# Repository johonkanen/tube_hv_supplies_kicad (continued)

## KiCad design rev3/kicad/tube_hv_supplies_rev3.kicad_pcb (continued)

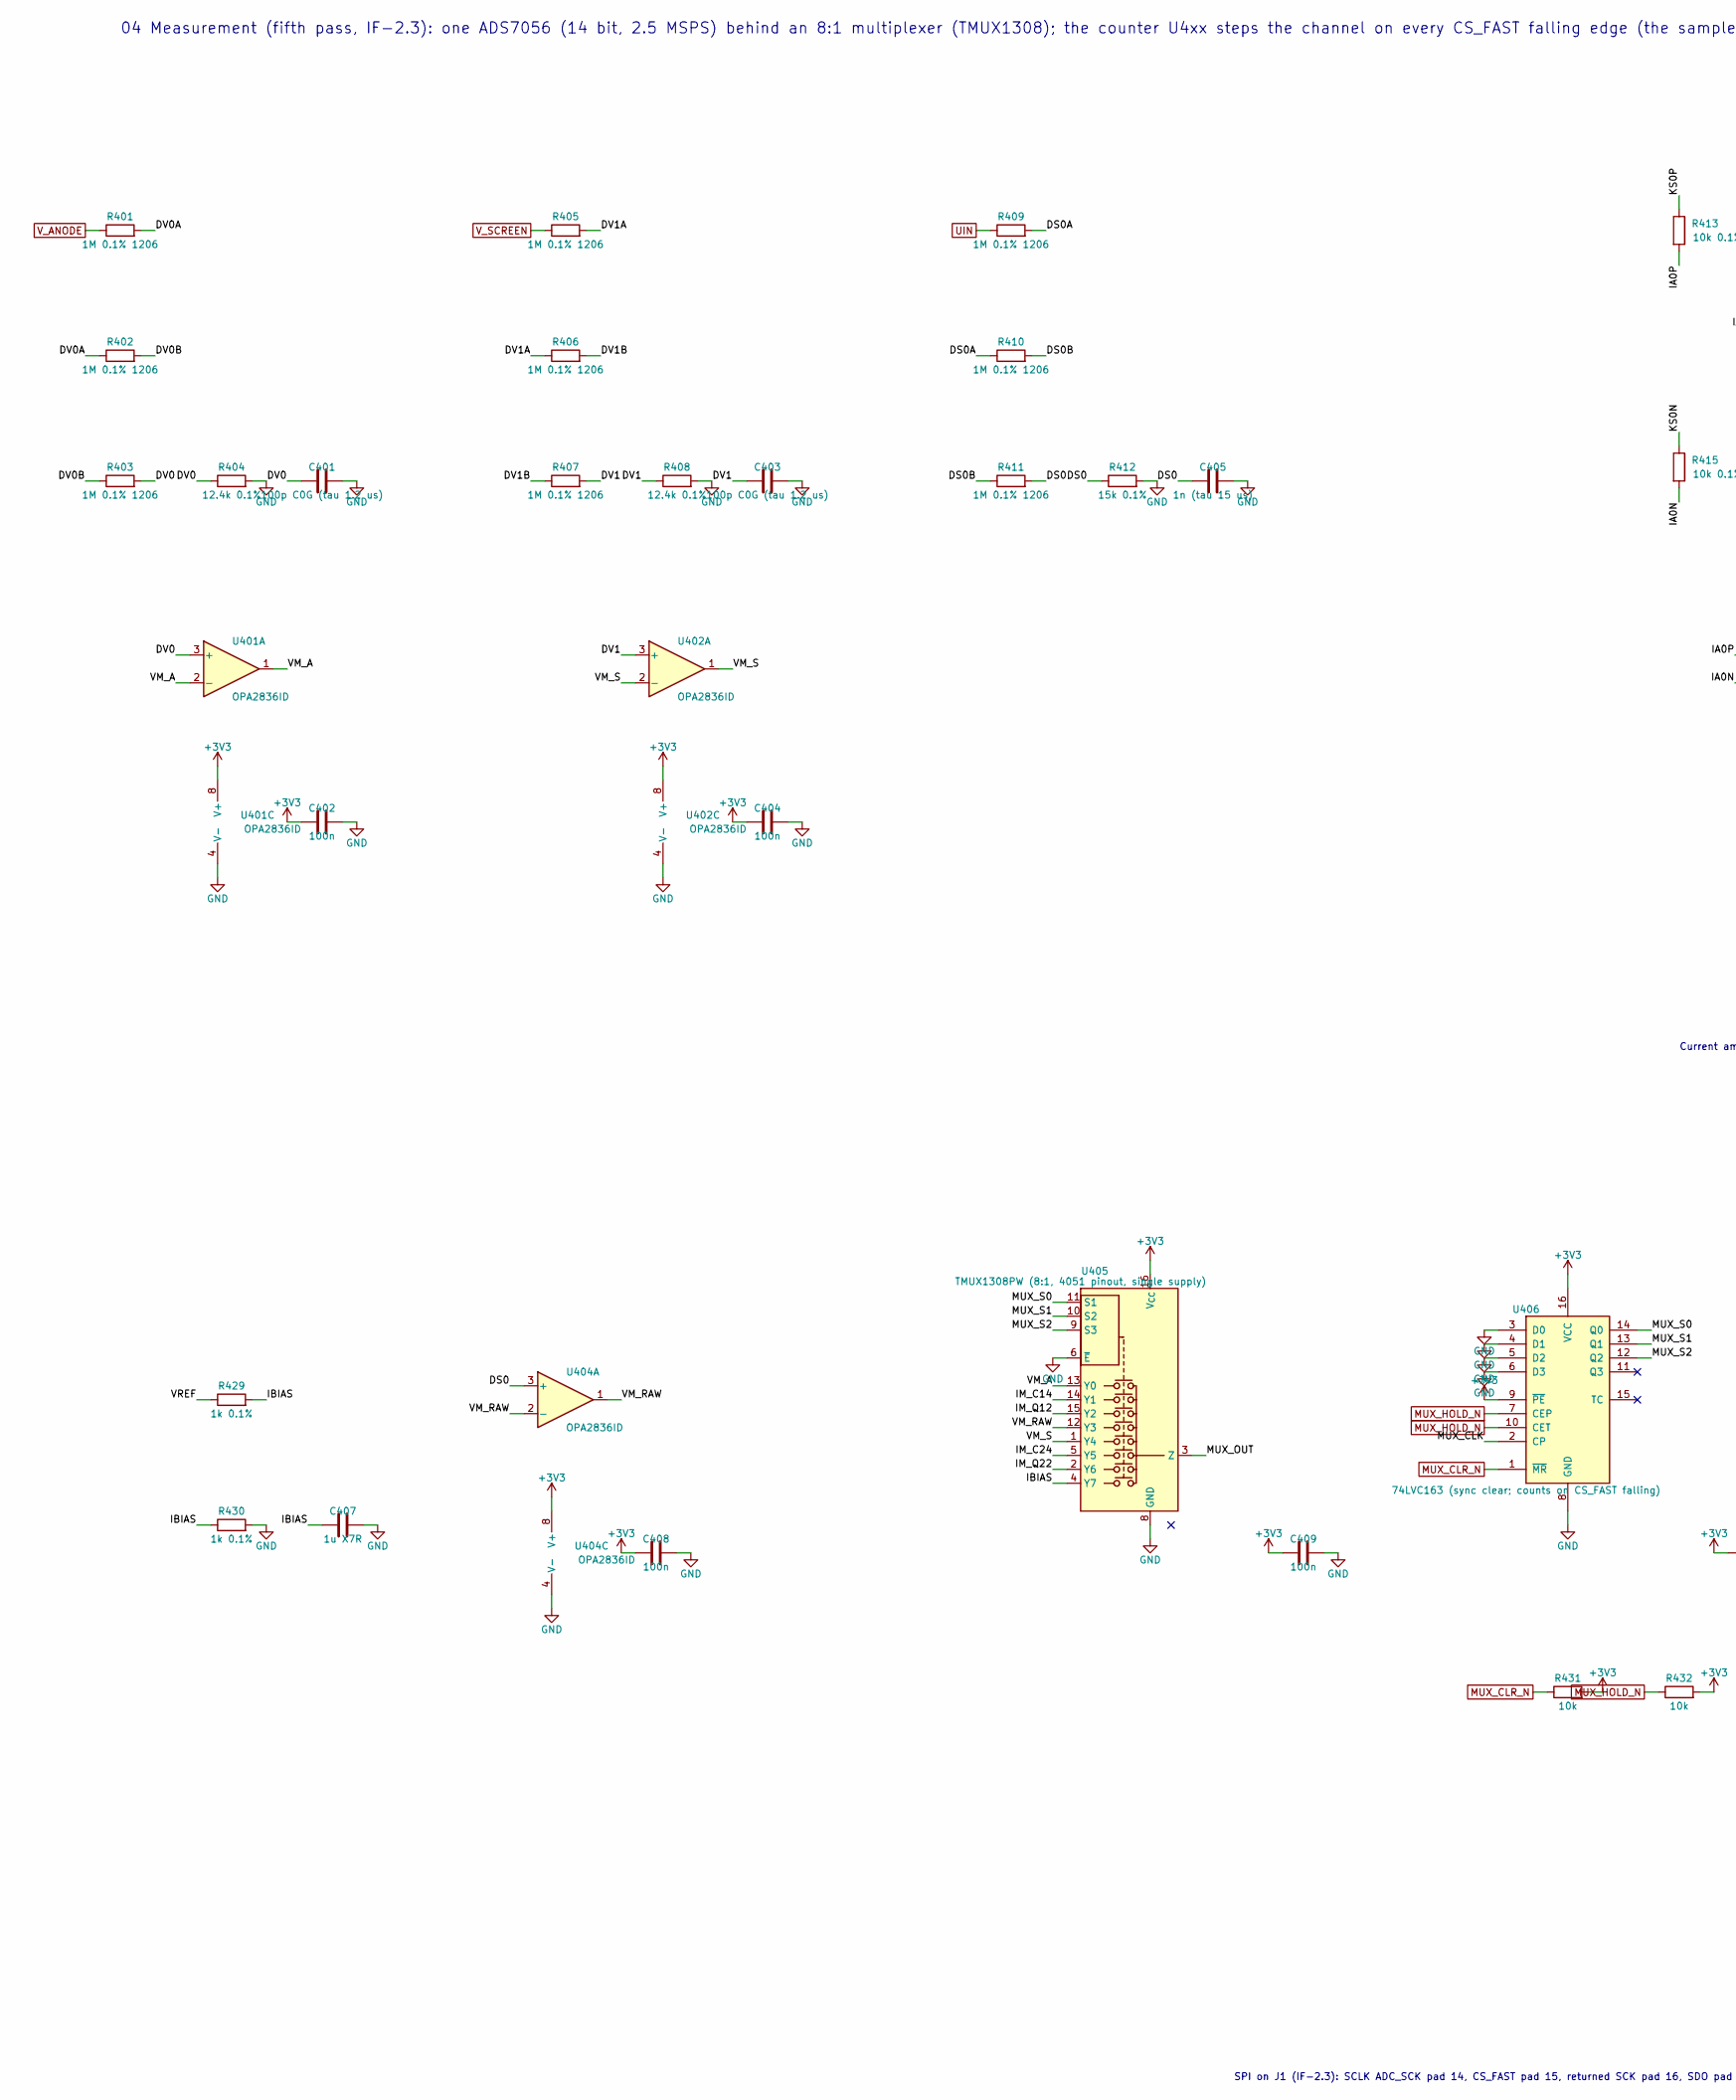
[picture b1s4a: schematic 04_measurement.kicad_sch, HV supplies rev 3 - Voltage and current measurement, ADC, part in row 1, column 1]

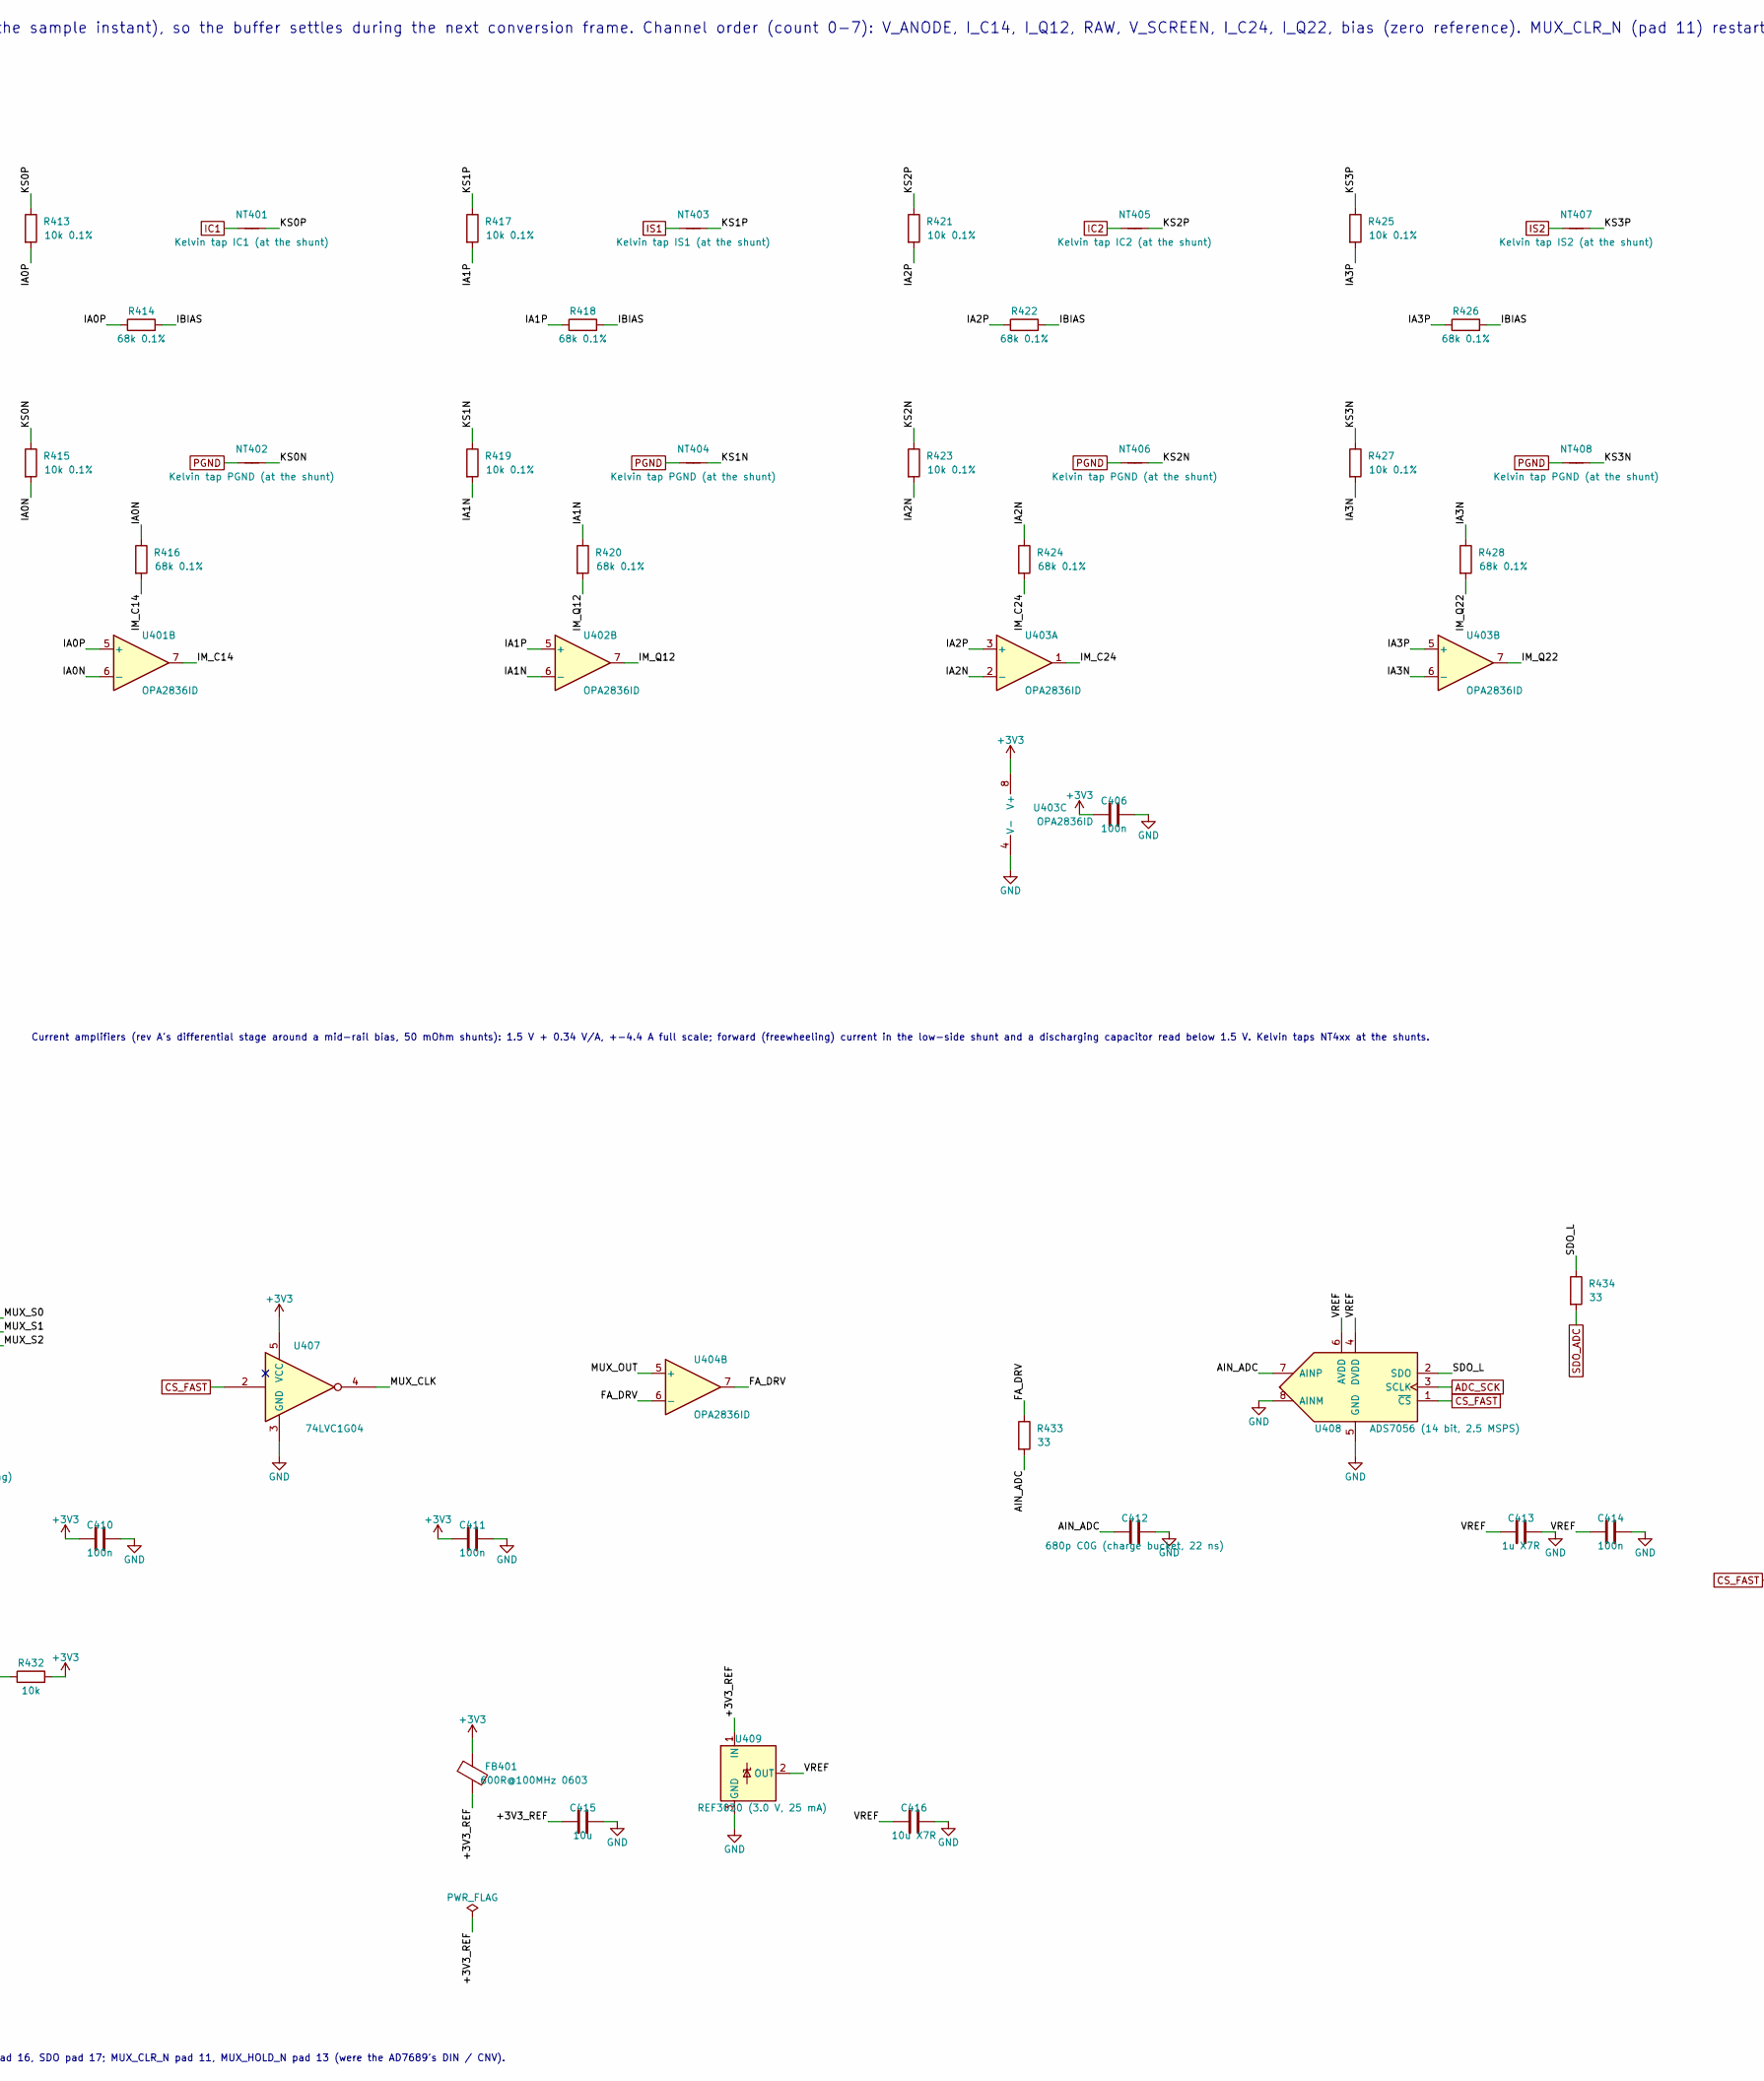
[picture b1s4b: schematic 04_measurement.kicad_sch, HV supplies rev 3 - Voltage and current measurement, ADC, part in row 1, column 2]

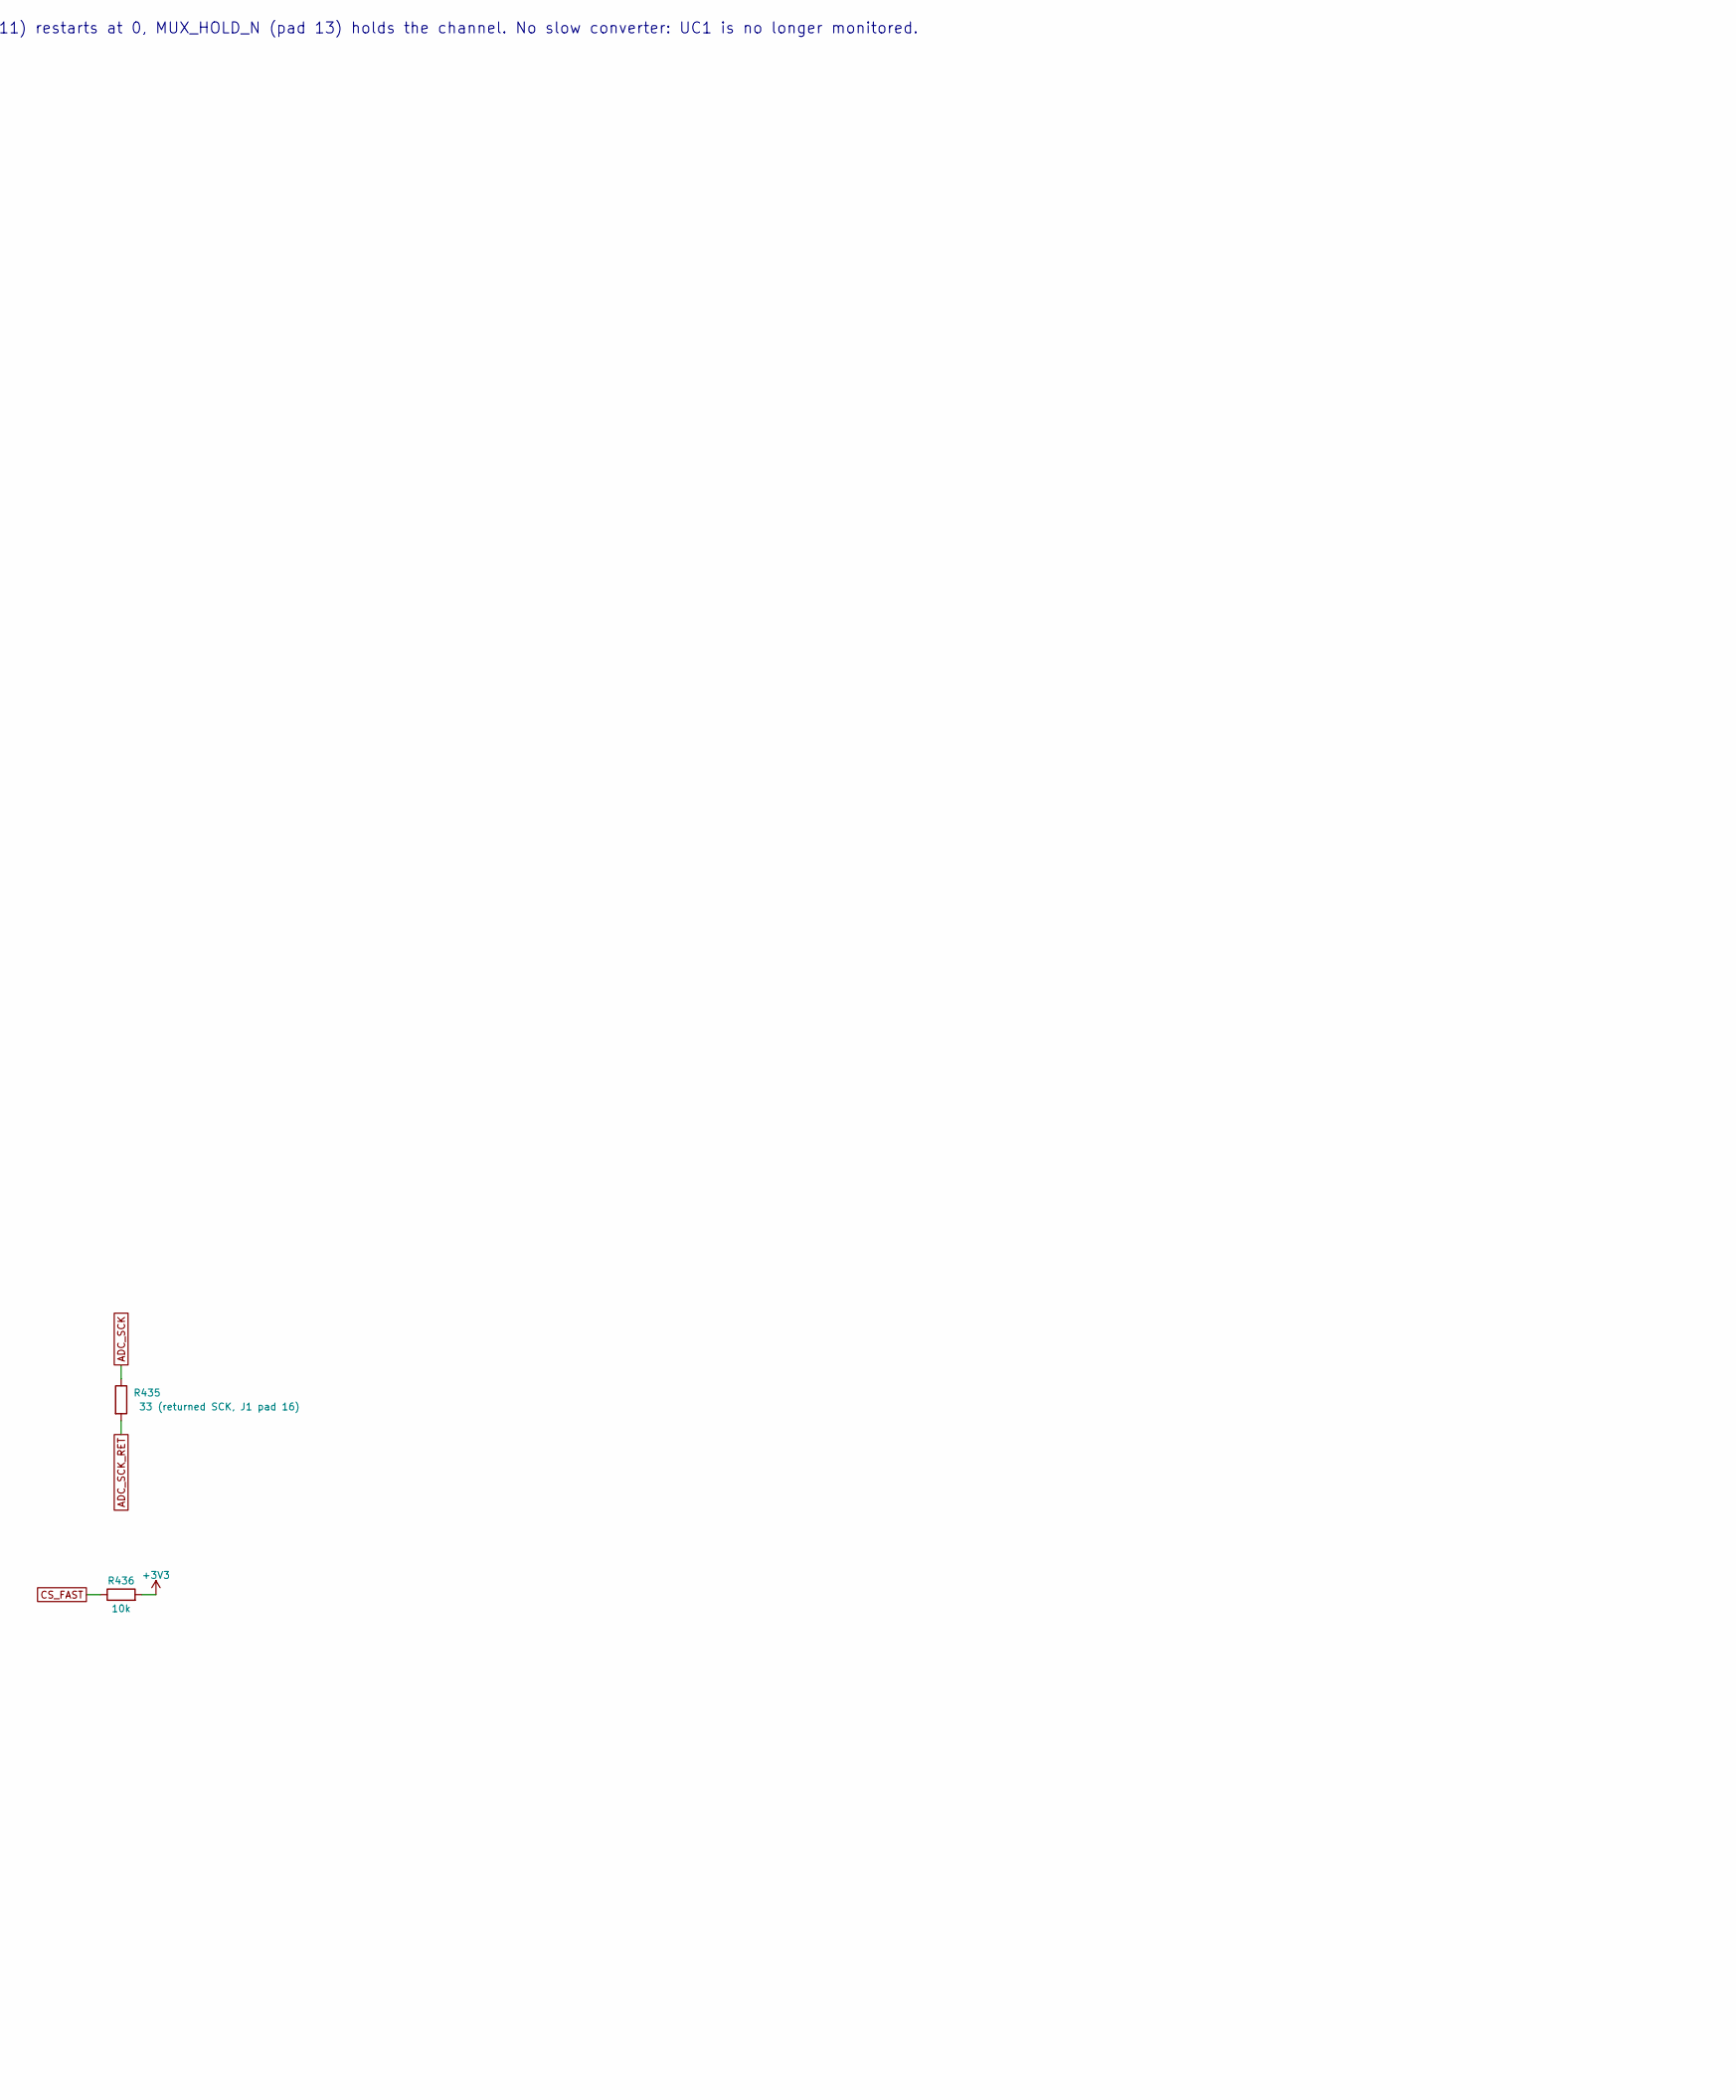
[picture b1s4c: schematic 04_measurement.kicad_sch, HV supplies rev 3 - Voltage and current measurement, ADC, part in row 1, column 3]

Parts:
C401, C403: 100p C0G (tau 1.2 us); C_0603_1608Metric
C402, C404, C406, C408, C409, C410, C411, C414: 100n; C_0603_1608Metric
C405: 1n (tau 15 us); C_0603_1608Metric
C407, C413: 1u X7R; C_0603_1608Metric
C412: 680p C0G (charge bucket, 22 ns); C_0603_1608Metric
C415: 10u; C_0805_2012Metric
C416: 10u X7R; C_0805_2012Metric
FB401: 600R@100MHz 0603; L_0603_1608Metric
NT401: Kelvin tap IC1 (at the shunt); NetTie-2_SMD_Pad0.5mm
NT402, NT404, NT406, NT408: Kelvin tap PGND (at the shunt); NetTie-2_SMD_Pad0.5mm
NT403: Kelvin tap IS1 (at the shunt); NetTie-2_SMD_Pad0.5mm
NT405: Kelvin tap IC2 (at the shunt); NetTie-2_SMD_Pad0.5mm
NT407: Kelvin tap IS2 (at the shunt); NetTie-2_SMD_Pad0.5mm
R401, R402, R403, R405, R406, R407, R409, R410, R411: 1M 0.1% 1206; R_1206_3216Metric
R404, R408: 12.4k 0.1%; R_0603_1608Metric
R412: 15k 0.1%; R_0603_1608Metric
R413, R415, R417, R419, R421, R423, R425, R427: 10k 0.1%; R_0603_1608Metric
R414, R416, R418, R420, R422, R424, R426, R428: 68k 0.1%; R_0603_1608Metric
R429, R430: 1k 0.1%; R_0603_1608Metric
R431, R432, R436: 10k; R_0603_1608Metric
R433, R434: 33; R_0603_1608Metric
R435: 33 (returned SCK, J1 pad 16); R_0603_1608Metric
U401, U402, U403, U404: OPA2836ID; SOIC-8_3.9x4.9mm_P1.27mm; MPN OPA2836IDR
U405: TMUX1308PW (8:1, 4051 pinout, single supply); TSSOP-16_4.4x5mm_P0.65mm; MPN TMUX1308PWR
U406: 74LVC163 (sync clear; counts on CS_FAST falling); TSSOP-16_4.4x5mm_P0.65mm; MPN SN74LVC163APWR
U407: 74LVC1G04; SOT-23-5; MPN SN74LVC1G04DBVR
U408: ADS7056 (14 bit, 2.5 MSPS); Texas_UQFN-8_1.5x1.5mm_P0.5mm; MPN ADS7056IRUGR
U409: REF3030 (3.0 V, 25 mA); SOT-23; MPN REF3030AIDBZR

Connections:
+3V3: C402.1, C404.1, C406.1, C408.1, C409.1, C410.1, C411.1, FB401.1, R431.2, R432.2, R436.2, U401.8 (V+), U402.8 (V+), U403.8 (V+), U404.8 (V+), U405.16 (V_{CC}), U406.9 (~PE), U406.16 (VCC), U407.5 (VCC); also elsewhere on the board
/04 Voltage and current measurement, ADC/+3V3_REF: C415.1, FB401.2, U409.1 (IN)
/04 Voltage and current measurement, ADC/AIN_ADC: C412.1, R433.2, U408.7 (AINP)
/04 Voltage and current measurement, ADC/DS0: C405.1, R411.2, R412.1, U404.3 (+)
/04 Voltage and current measurement, ADC/DS0A: R409.2, R410.1
/04 Voltage and current measurement, ADC/DS0B: R410.2, R411.1
/04 Voltage and current measurement, ADC/DV0: C401.1, R403.2, R404.1, U401.3 (+)
/04 Voltage and current measurement, ADC/DV0A: R401.2, R402.1
/04 Voltage and current measurement, ADC/DV0B: R402.2, R403.1
/04 Voltage and current measurement, ADC/DV1: C403.1, R407.2, R408.1, U402.3 (+)
/04 Voltage and current measurement, ADC/DV1A: R405.2, R406.1
/04 Voltage and current measurement, ADC/DV1B: R406.2, R407.1
/04 Voltage and current measurement, ADC/FA_DRV: R433.1, U404.6 (-), U404.7
/04 Voltage and current measurement, ADC/IA0N: R415.2, R416.1, U401.6 (-)
/04 Voltage and current measurement, ADC/IA0P: R413.2, R414.1, U401.5 (+)
/04 Voltage and current measurement, ADC/IA1N: R419.2, R420.1, U402.6 (-)
/04 Voltage and current measurement, ADC/IA1P: R417.2, R418.1, U402.5 (+)
/04 Voltage and current measurement, ADC/IA2N: R423.2, R424.1, U403.2 (-)
/04 Voltage and current measurement, ADC/IA2P: R421.2, R422.1, U403.3 (+)
/04 Voltage and current measurement, ADC/IA3N: R427.2, R428.1, U403.6 (-)
/04 Voltage and current measurement, ADC/IA3P: R425.2, R426.1, U403.5 (+)
/04 Voltage and current measurement, ADC/IBIAS: C407.1, R414.2, R418.2, R422.2, R426.2, R429.2, R430.1, U405.4 (Y7)
/04 Voltage and current measurement, ADC/IM_C14: R416.2, U401.7, U405.14 (Y1)
/04 Voltage and current measurement, ADC/IM_C24: R424.2, U403.1, U405.5 (Y5)
/04 Voltage and current measurement, ADC/IM_Q12: R420.2, U402.7, U405.15 (Y2)
/04 Voltage and current measurement, ADC/IM_Q22: R428.2, U403.7, U405.2 (Y6)
/04 Voltage and current measurement, ADC/KS0N: NT402.2, R415.1
/04 Voltage and current measurement, ADC/KS0P: NT401.2, R413.1
/04 Voltage and current measurement, ADC/KS1N: NT404.2, R419.1
/04 Voltage and current measurement, ADC/KS1P: NT403.2, R417.1
/04 Voltage and current measurement, ADC/KS2N: NT406.2, R423.1
/04 Voltage and current measurement, ADC/KS2P: NT405.2, R421.1
/04 Voltage and current measurement, ADC/KS3N: NT408.2, R427.1
/04 Voltage and current measurement, ADC/KS3P: NT407.2, R425.1
/04 Voltage and current measurement, ADC/MUX_CLK: U406.2 (CP), U407.4
/04 Voltage and current measurement, ADC/MUX_OUT: U404.5 (+), U405.3 (Z)
/04 Voltage and current measurement, ADC/MUX_S0: U405.11 (S1), U406.14 (Q0)
/04 Voltage and current measurement, ADC/MUX_S1: U405.10 (S2), U406.13 (Q1)
/04 Voltage and current measurement, ADC/MUX_S2: U405.9 (S3), U406.12 (Q2)
/04 Voltage and current measurement, ADC/SDO_L: R434.1, U408.2 (SDO)
/04 Voltage and current measurement, ADC/VM_A: U401.1, U401.2 (-), U405.13 (Y0)
/04 Voltage and current measurement, ADC/VM_RAW: U404.1, U404.2 (-), U405.12 (Y3)
/04 Voltage and current measurement, ADC/VM_S: U402.1, U402.2 (-), U405.1 (Y4)
/04 Voltage and current measurement, ADC/VREF: C413.1, C414.1, C416.1, R429.1, U408.4 (DVDD), U408.6 (AVDD), U409.2 (OUT)
ADC_SCK: R435.1, U408.3 (SCLK); also elsewhere on the board
ADC_SCK_RET: R435.2; also elsewhere on the board
CS_FAST: R436.1, U407.2, U408.1 (~CS); also elsewhere on the board
GND: C401.2, C402.2, C403.2, C404.2, C405.2, C406.2, C407.2, C408.2, C409.2, C410.2, C411.2, C412.2, C413.2, C414.2, C415.2, C416.2, R404.2, R408.2, R412.2, R430.2, U401.4 (V-), U402.4 (V-), U403.4 (V-), U404.4 (V-), U405.6 (~E), U405.8 (GND), U406.3 (D0), U406.4 (D1), U406.5 (D2), U406.6 (D3), U406.8 (GND), U407.3 (GND), U408.5 (GND), U408.8 (AINM), U409.3 (GND); also elsewhere on the board
IC1: NT401.1; also elsewhere on the board
IC2: NT405.1; also elsewhere on the board
IS1: NT403.1; also elsewhere on the board
IS2: NT407.1; also elsewhere on the board
MUX_CLR_N: R431.1, U406.1 (~MR); also elsewhere on the board
MUX_HOLD_N: R432.1, U406.7 (CEP), U406.10 (CET); also elsewhere on the board
PGND: NT402.1, NT404.1, NT406.1, NT408.1; also elsewhere on the board
SDO_ADC: R434.2; also elsewhere on the board
UIN: R409.1; also elsewhere on the board
V_ANODE: R401.1; also elsewhere on the board
V_SCREEN: R405.1; also elsewhere on the board

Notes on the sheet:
04 Measurement (fifth pass, IF-2.3): one ADS7056 (14 bit, 2.5 MSPS) behind an 8:1 multiplexer (TMUX1308); the counter U4xx steps the channel on every CS_FAST falling edge (the sample instant), so the buffer settles during the next conversion frame. Channel order (count 0-7): V_ANODE, I_C14, I_Q12, 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
Current amplifiers (rev A's differential stage around a mid-rail bias, 50 mOhm shunts): 1.5 V + 0.34 V/A, +-4.4 A full scale; forward (freewheeling) current in the low-side shunt and a discharging capacitor read below 1.5 V. Kelvin taps NT4xx at the shunts.
SPI on J1 (IF-2.3): SCLK ADC_SCK pad 14, CS_FAST pad 15, returned SCK pad 16, SDO pad 17; MUX_CLR_N pad 11, MUX_HOLD_N pad 13 (were the AD7689's DIN / CNV).

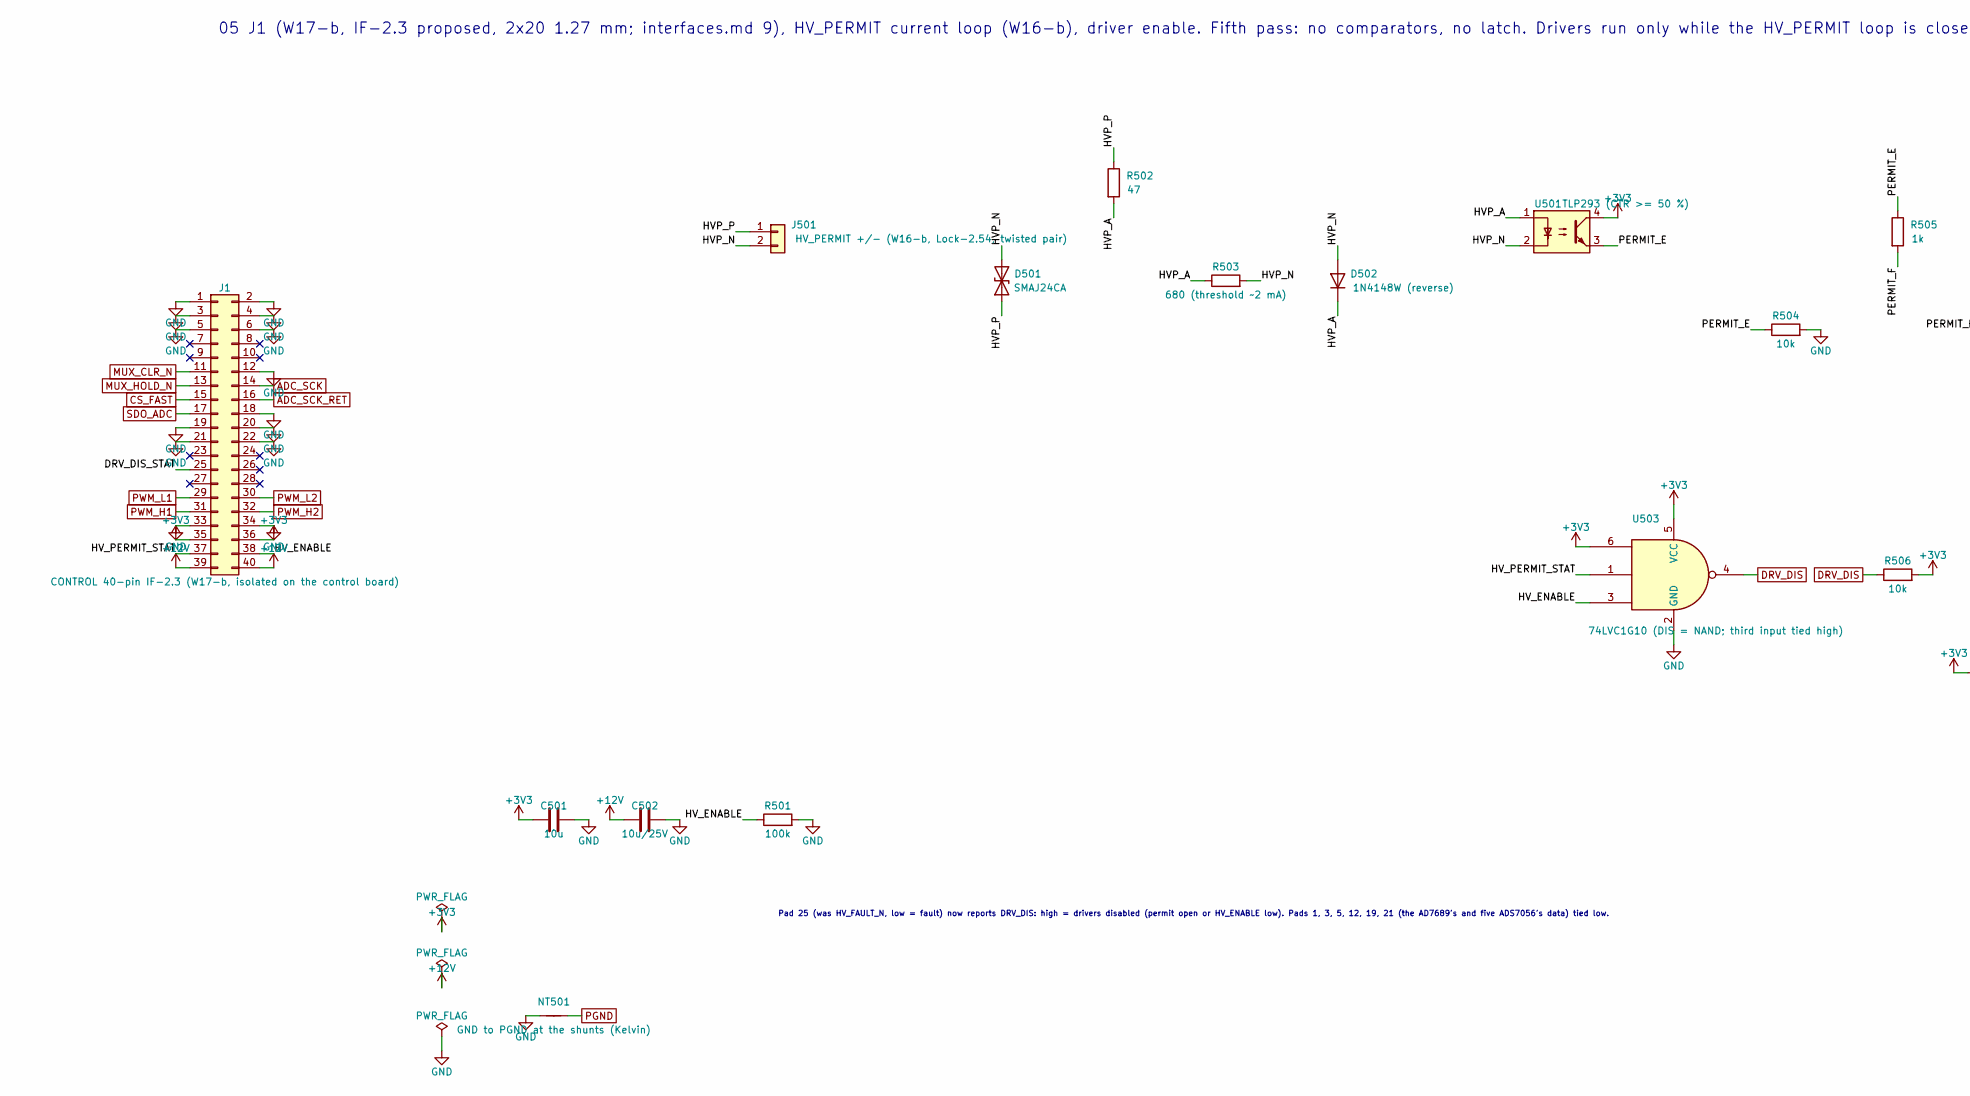
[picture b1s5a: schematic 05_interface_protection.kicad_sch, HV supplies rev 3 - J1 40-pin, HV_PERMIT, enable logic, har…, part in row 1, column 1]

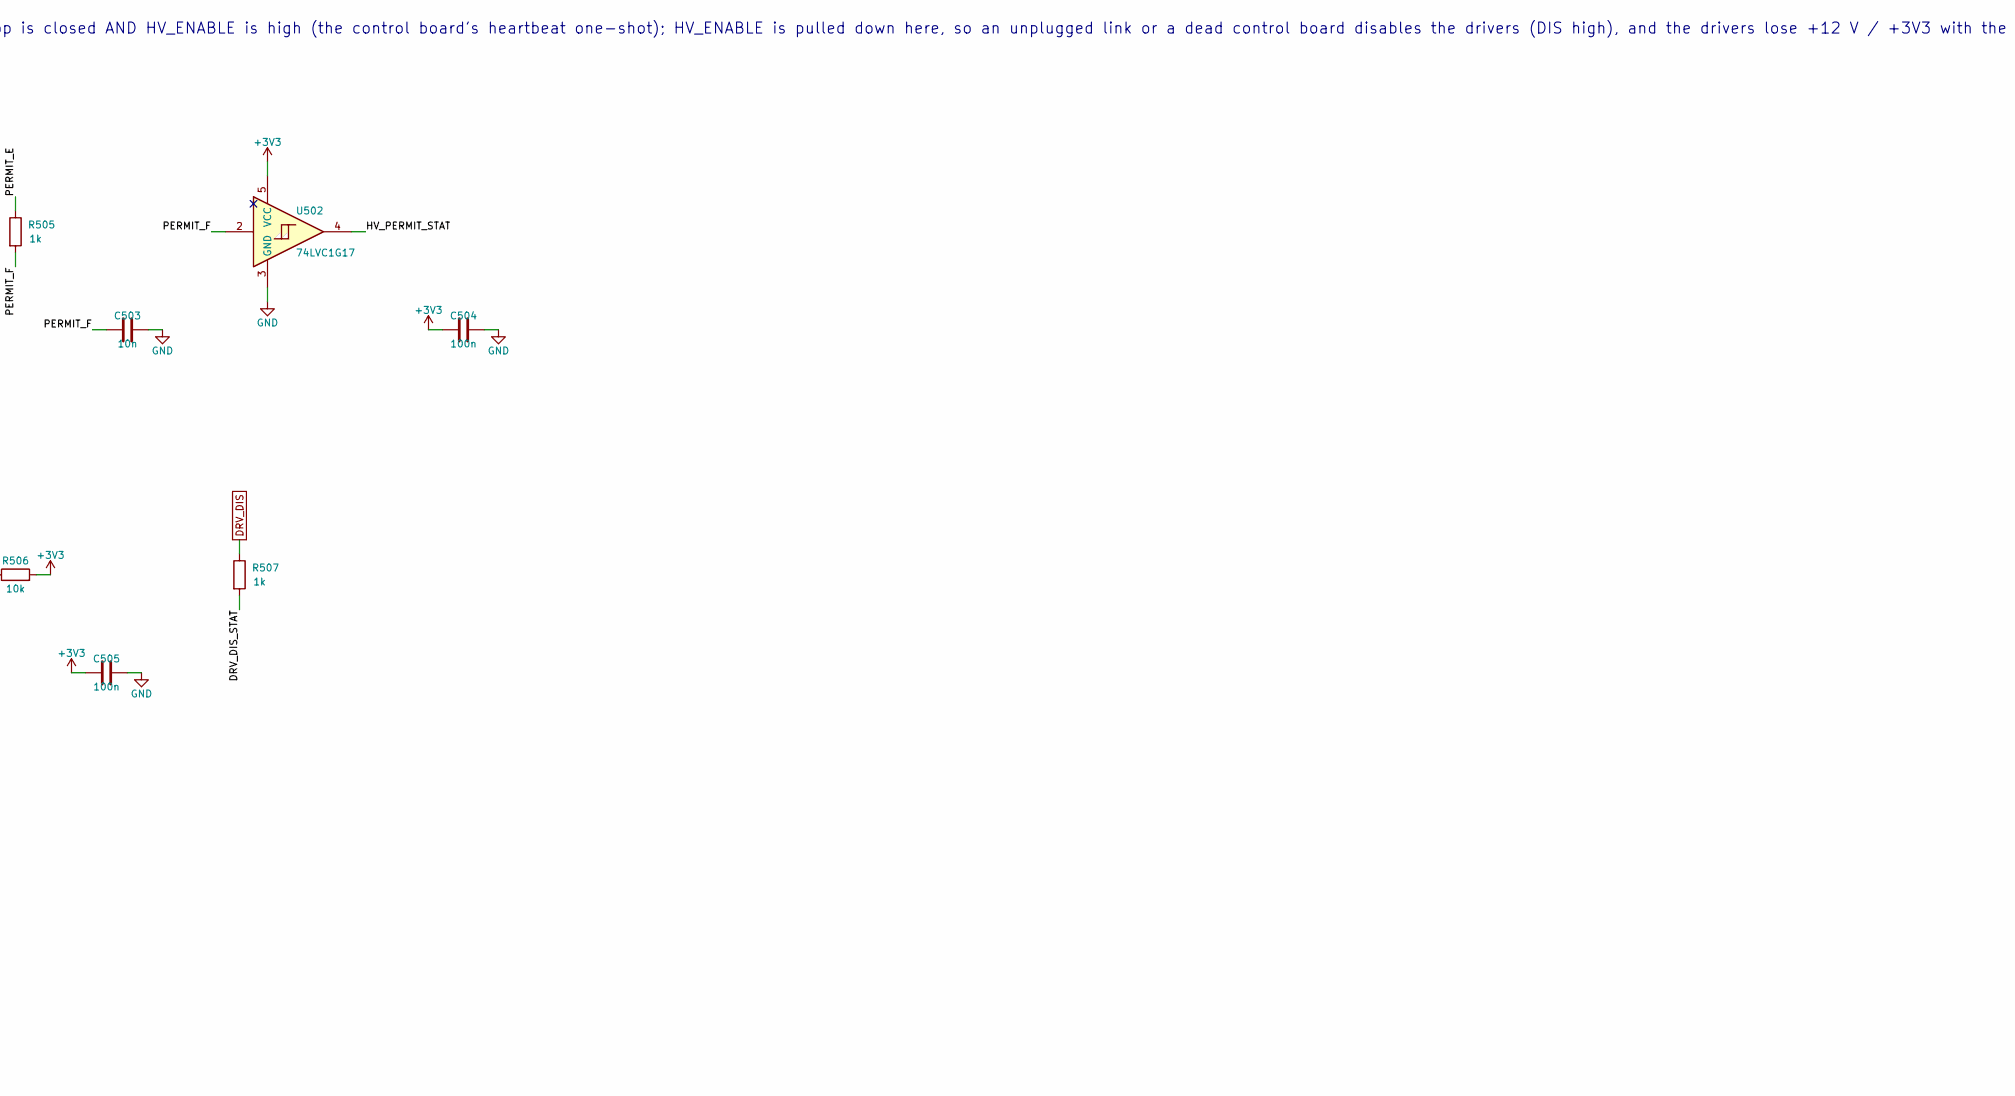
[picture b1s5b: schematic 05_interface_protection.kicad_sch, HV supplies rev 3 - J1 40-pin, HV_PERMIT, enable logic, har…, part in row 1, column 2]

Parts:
C501: 10u; C_0805_2012Metric
C502: 10u/25V; C_1206_3216Metric
C503: 10n; C_0603_1608Metric
C504, C505: 100n; C_0603_1608Metric
D501: SMAJ24CA; D_SMA; MPN SMAJ24CA
D502: 1N4148W (reverse); D_SOD-123; MPN 1N4148W
J1: CONTROL 40-pin IF-2.3 (W17-b, isolated on the con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; PinHeader_2x20_P1.27mm_Vertical; MPN Samtec SHF-120-01-L-D-TH
J501: HV_PERMIT +/- (W16-b, Lock-2.54, twisted pair); Molex_KK-254_AE-6410-02A_1x02_P2.54mm_Vertical; MPN Molex 22-27-2021
NT501: GND to PGND at the shunts (Kelvin); NetTie-2_SMD_Pad0.5mm
R501: 100k; R_0603_1608Metric
R502: 47; R_0603_1608Metric
R503: 680 (threshold ~2 mA); R_0603_1608Metric
R504, R506: 10k; R_0603_1608Metric
R505, R507: 1k; R_0603_1608Metric
U501: TLP293 (CTR >= 50 %); SOIC-4_4.55x2.6mm_P1.27mm; MPN TLP293(GB-TPL,E)
U502: 74LVC1G17; SOT-23-5; MPN SN74LVC1G17DBVR
U503: 74LVC1G10 (DIS = NAND; third input tied high); SOT-23-6; MPN SN74LVC1G10DBVR

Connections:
+3V3: C501.1, C504.1, C505.1, J1.35, J1.36, R506.2, U501.4, U502.5 (VCC), U503.5 (VCC), U503.6; also elsewhere on the board
+12V: C502.1, J1.39, J1.40; also elsewhere on the board
/05 J1 40-pin, HV_PERMIT, enable logic, hardware protection/DRV_DIS_STAT: J1.25, R507.2
/05 J1 40-pin, HV_PERMIT, enable logic, hardware protection/HVP_A: D502.1 (K), R502.2, R503.1, U501.1
/05 J1 40-pin, HV_PERMIT, enable logic, hardware protection/HVP_N: D501.2 (A2), D502.2 (A), J501.2, R503.2, U501.2
/05 J1 40-pin, HV_PERMIT, enable logic, hardware protection/HVP_P: D501.1 (A1), J501.1, R502.1
/05 J1 40-pin, HV_PERMIT, enable logic, hardware protection/HV_ENABLE: J1.38, R501.1, U503.3
/05 J1 40-pin, HV_PERMIT, enable logic, hardware protection/HV_PERMIT_STAT: J1.37, U502.4, U503.1
/05 J1 40-pin, HV_PERMIT, enable logic, hardware protection/PERMIT_E: R504.1, R505.1, U501.3
/05 J1 40-pin, HV_PERMIT, enable logic, hardware protection/PERMIT_F: C503.1, R505.2, U502.2
ADC_SCK: J1.14; also elsewhere on the board
ADC_SCK_RET: J1.16; also elsewhere on the board
CS_FAST: J1.15; also elsewhere on the board
DRV_DIS: R506.1, R507.1, U503.4; also elsewhere on the board
GND: C501.2, C502.2, C503.2, C504.2, C505.2, J1.1, J1.2, J1.3, J1.4, J1.5, J1.6, J1.12, J1.18, J1.19, J1.20, J1.21, J1.22, J1.33, J1.34, NT501.1, R501.2, R504.2, U502.3 (GND), U503.2 (GND); also elsewhere on the board
MUX_CLR_N: J1.11; also elsewhere on the board
MUX_HOLD_N: J1.13; also elsewhere on the board
PGND: NT501.2; also elsewhere on the board
PWM_H1: J1.31; also elsewhere on the board
PWM_H2: J1.32; also elsewhere on the board
PWM_L1: J1.29; also elsewhere on the board
PWM_L2: J1.30; also elsewhere on the board
SDO_ADC: J1.17; also elsewhere on the board

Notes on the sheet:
05 J1 (W17-b, IF-2.3 proposed, 2x20 1.27 mm; interfaces.md 9), HV_PERMIT current loop (W16-b), driver enable. Fifth pass: no comparators, no latch. Drivers run only while the HV_PERMIT loop is closed AND HV_ENABLE is high (the control board's heartbeat one-shot); HV_ENABLE is pulled down here, so a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
Pad 25 (was HV_FAULT_N, low = fault) now reports DRV_DIS: high = drivers disabled (permit open or HV_ENABLE low). Pads 1, 3, 5, 12, 19, 21 (the AD7689's and five ADS7056's data) tied low.
